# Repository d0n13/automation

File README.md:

# automation
Homebridge accessories

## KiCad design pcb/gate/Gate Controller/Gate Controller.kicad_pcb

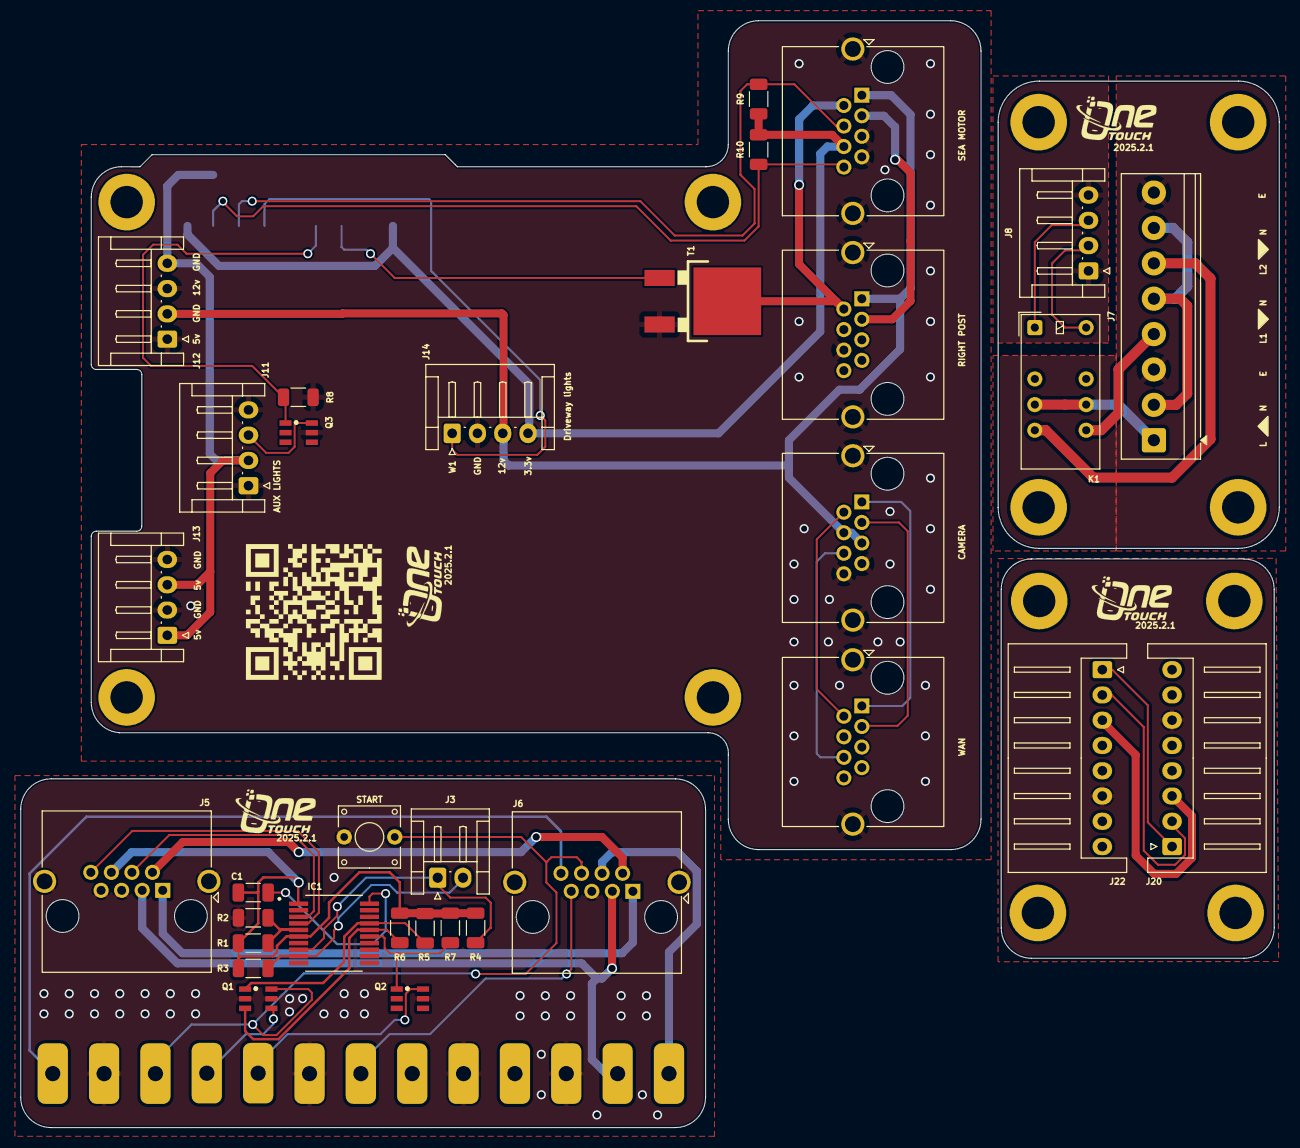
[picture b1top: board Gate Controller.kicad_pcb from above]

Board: 2 copper layers, 124.5 x 109.5 mm, 52 parts (1 on the bottom side), 39 nets.

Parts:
C1: 0.1uF; C_1206_3216Metric
G1, G2, G3, G4: LOGO; onetouchlogo
IC1: MCP23009-E_SS; SOP65P780X200-20N
J3: CN7; JST_EH_S2B-EH_1x02_P2.50mm_Horizontal
J4: CN1; Gate_Connector_2022
J5, J6, J16, J17: RJ45_Shielded; RJ45_Amphenol_RJHSE5380
J7: AUX; TerminalBlock_Phoenix_PT-1,5-8-3.5-H_1x08_P3.50mm_Horizontal
J8, J11: AUX; JST_EH_S4B-EH_1x04_P2.50mm_Horizontal
J12: Power; JST_EH_S4B-EH_1x04_P2.50mm_Horizontal
J13: Fiber Power; JST_EH_S4B-EH_1x04_P2.50mm_Horizontal
J14: Driveway lights; JST_EH_S4B-EH_1x04_P2.50mm_Horizontal
J15: POE Camera; RJ45_Amphenol_RJHSE5380
J18: Ethernet; RJ45_Amphenol_RJHSE5380
J20: Pi; JST_XH_S8B-XH-A_1x08_P2.50mm_Horizontal
J22: Post; JST_XH_S8B-XH-A_1x08_P2.50mm_Horizontal
K1: EC2-5SNU; Relay_DPDT_Kemet_EC2
MK1, MK2, MK3, MK4, MK5, MK6, MK7, MK8, MK9, MK10, MK11, MK12: M3.2; MountingHole_3.2mm_M3_DIN965_Pad
P1: pi; PinSocket_2x10_P2.54mm_Vertical_SMD
Q1, Q2, Q3: FDC6561AN; SSOT-6
R1: 1K; R_1206_3216Metric
R2: 15K; R_1206_3216Metric
R3, R4, R5, R6, R7, R8: 10k; R_1206_3216Metric
R9, R10: 1.8K; R_1206_3216Metric
SW1: START; TS-D015
T1: STD40NF10; D_PAK
U2: QRCode Github Automation

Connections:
3V3: C1.2, IC1.1 (VDD), IC1.6 (~RESET), J5.6, J14.4, J17.6, P1.1, P1.17, R1.1, R3.2, R4.2, R5.2, R6.2, R7.2, R9.2, R10.2
+5v: J11.2, J12.4, J13.1, J13.3, P1.2, P1.4
+12V: J12.2, J14.3, J15.4, J15.5, J16.1, J17.1
+12v: J5.1, J6.1
ANTENNA+: J4.1, J6.8
CN1_24v(FL): J4.12, J5.3, J6.3, J16.3, J17.3, J20.3, J22.3
CN1_(FL)-: J4.13, J6.4
E: J7.3, J7.8
GATE_LED_12V: J20.1, J22.1
GATE_LED_COM: J5.2, J6.2, J16.2, J17.2, T1.2 (D)
GND: J4.2, J4.6, J4.9, J4.11, J5.5, J5.7, J5.SH, J6.5, J6.SH, J8.1, J8.4, J11.1, J11.4, J12.1, J12.3, J13.2, J13.4, J14.2, J15.7, J15.8, J15.SH, J16.6, J16.SH, J17.5, J17.7, J17.SH, J18.SH, J20.6, J22.6, P1.6, P1.9, P1.14, P1.20, Q1.2, Q1.5, Q2.5, Q3.5, R2.2, R8.2, SW1.2, T1.3 (S)
L: J7.1, K1.4, K1.9
L1: J7.4, K1.8
L2: J7.6, K1.5
N: J7.2, J7.5, J7.7
unnamed: IC1.5 (ADDR), R1.2, R2.1
unnamed: IC1.8 (GP0), J3.1, R4.1
unnamed: IC1.9 (GP1), J3.2, R3.1
unnamed: IC1.15 (GP5), Q2.1, R7.1
unnamed: IC1.16 (GP6), Q1.3, R6.1
unnamed: IC1.17 (GP7), Q1.1, R5.1
unnamed: C1.1, IC1.20 (VSS)
unnamed: J8.2, K1.12
unnamed: J8.3, K1.1
unnamed: J11.3, Q3.6
unnamed: J15.1, J18.1
unnamed: J15.2, J18.2
unnamed: J15.3, J18.3
unnamed: J15.6, J18.6
unnamed: J20.2, J22.2
PEDST: J4.4, Q1.4
PH1: J4.7, J6.7
Rpi11: P1.11, Q3.1, R8.1
Rpi13: P1.13, T1.1 (G)
SCL1: IC1.3 (SCL), J5.4, J17.4, P1.5, R9.1
SDA1: IC1.4 (SDA), J5.8, J17.8, P1.3, R10.1
START: J4.3, J6.6, Q1.6, SW1.1
STOP: J4.5, Q2.6
W1: J14.1, P1.7

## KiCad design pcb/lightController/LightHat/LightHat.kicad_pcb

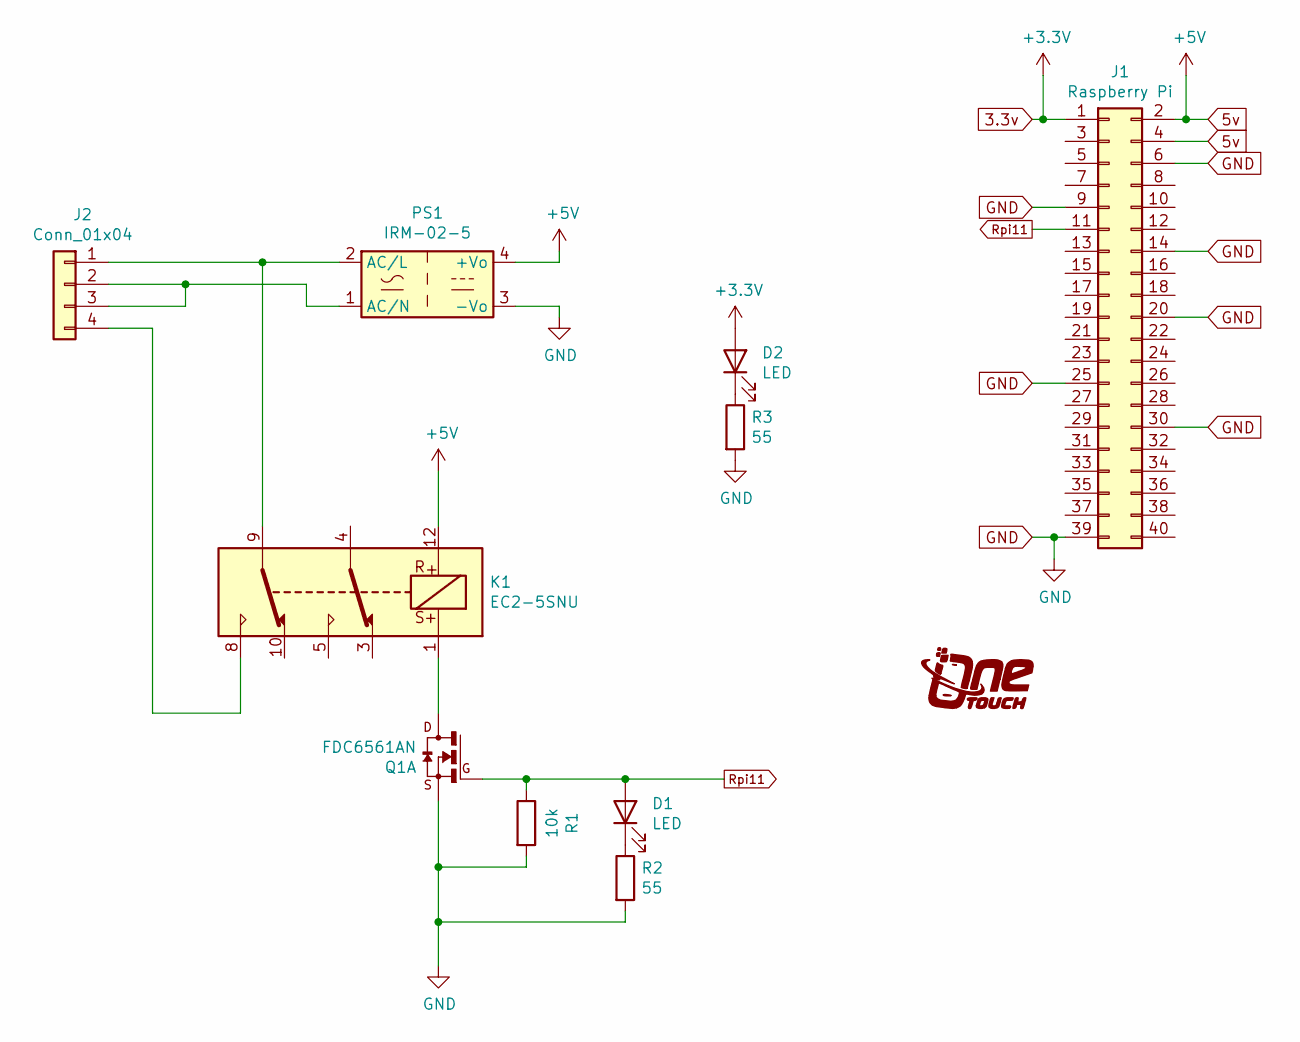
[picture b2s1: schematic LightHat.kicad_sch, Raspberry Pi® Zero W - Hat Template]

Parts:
D1, D2: LED; LED_0603_1608Metric
G1: LOGO; onetouchlogo
J1: Raspberry Pi; PinHeader_2x20_P2.54mm_Vertical
J2: Conn_01x04; TerminalBlock_bornier-4_P5.08mm
K1: EC2-5SNU; Relay_DPDT_Kemet_EC2
PS1: IRM-02-5; Converter_ACDC_MeanWell_IRM-02-xx_THT
Q1: FDC6561AN; SSOT-6
R1: 10k; R_0603_1608Metric_Pad0.98x0.95mm_HandSolder
R2, R3: 55; R_0805_2012Metric

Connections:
3.3v: D2.2 (A), J1.1
5v: J1.2, J1.4, K1.12, PS1.4 (+Vo)
GND: J1.6, J1.9, J1.14, J1.20, J1.25, J1.30, J1.39, PS1.3 (-Vo), Q1.5, R1.2, R2.2, R3.2
unnamed: D1.1 (K), R2.1
unnamed: D2.1 (K), R3.1
unnamed: J2.1, K1.9, PS1.2 (AC/L)
unnamed: J2.2, J2.3, PS1.1 (AC/N)
unnamed: J2.4, K1.8
unnamed: K1.1, Q1.6
Rpi11: D1.2 (A), J1.11, Q1.1, R1.1

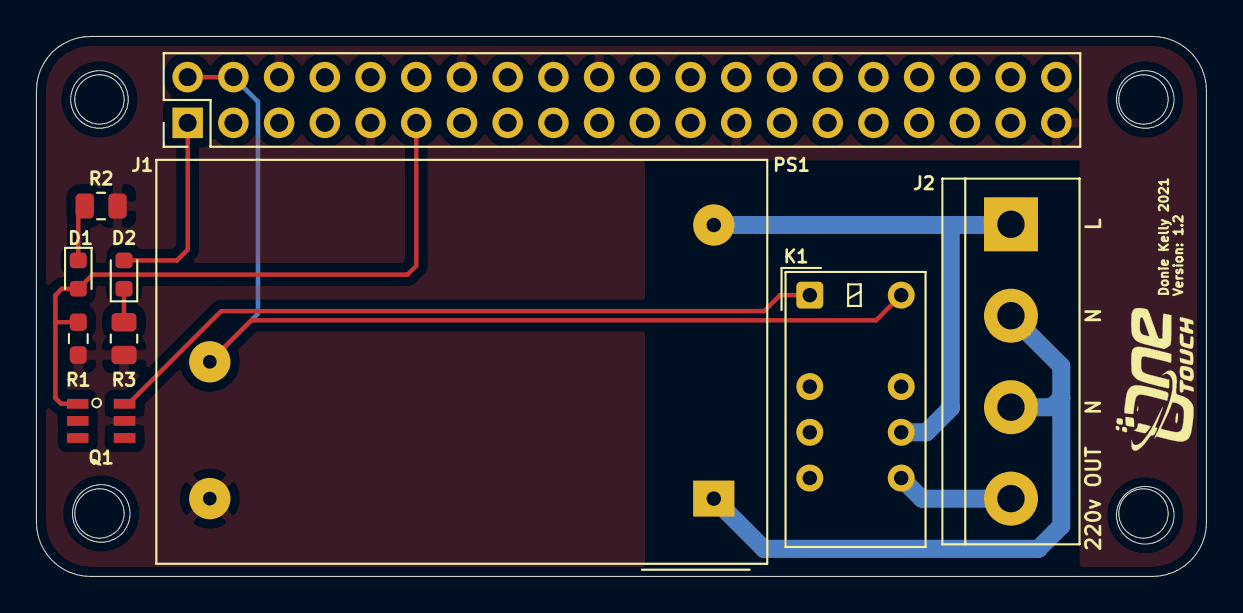
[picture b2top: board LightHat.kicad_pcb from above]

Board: 2 copper layers, 65.0 x 30.0 mm, 11 parts (0 on the bottom side), 10 nets.

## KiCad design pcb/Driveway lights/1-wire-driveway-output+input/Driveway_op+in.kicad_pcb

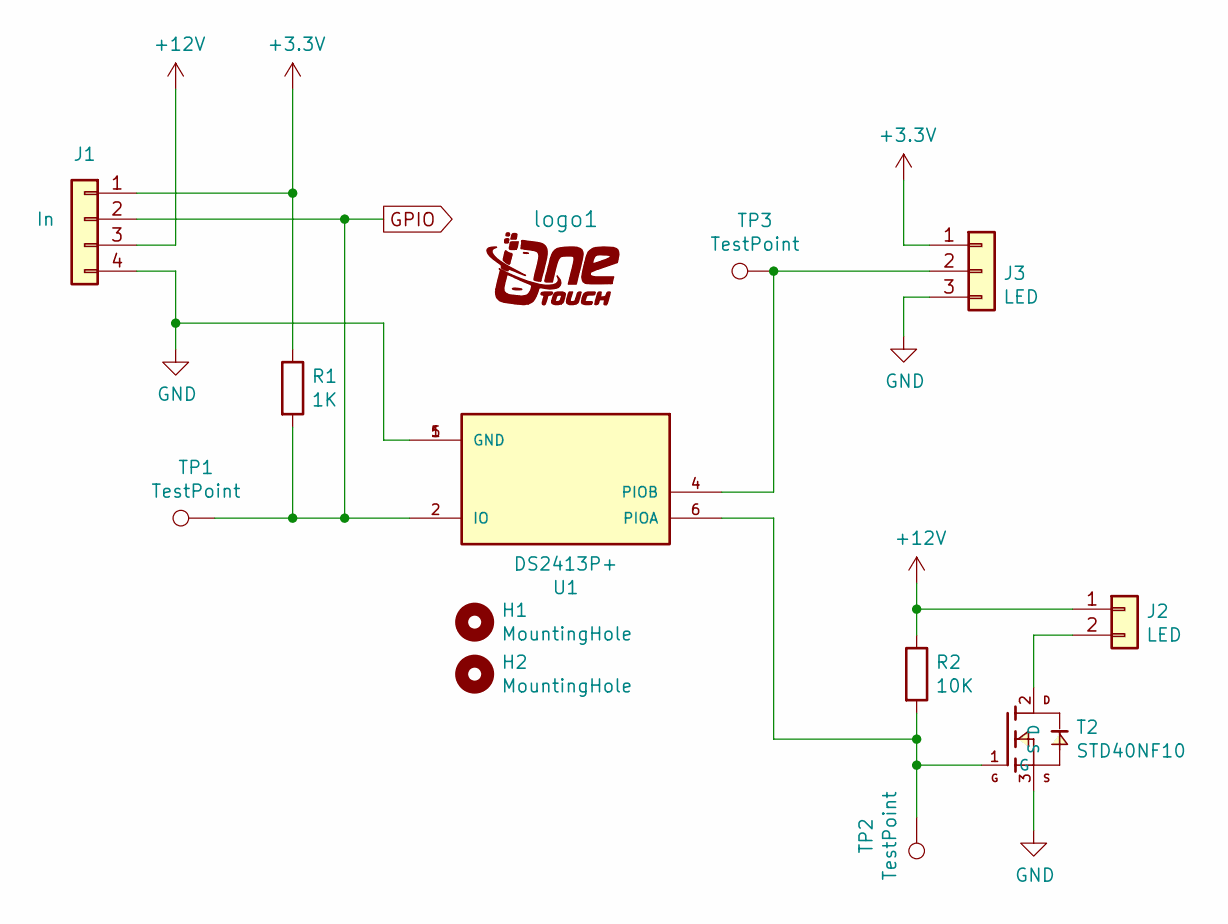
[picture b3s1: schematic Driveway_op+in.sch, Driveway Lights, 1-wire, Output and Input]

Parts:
H1, H2: MountingHole; MountingHole_2.1mm
J1: In; JST_EH_S4B-EH_1x04_P2.50mm_Horizontal
J2: LED; JST_EH_S2B-EH_1x02_P2.50mm_Horizontal
J3: LED; JST_XH_S3B-XH-A-1_1x03_P2.50mm_Horizontal
R1: 1K; R_1206_3216Metric
R2: 10K; R_1206_3216Metric
T2: STD40NF10; D_PAK
TP1, TP2, TP3: TestPoint; TestPoint_Pad_1.0x1.0mm
U1: DS2413P+; SOIC127P429X150-N
logo1: LOGO; onetouchlogo

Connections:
+3V3: J1.1, J3.1, R1.1
+12V: J1.3, J2.1, R2.1
GND: J1.4, J3.3, T2.3 (S), U1.1 (GND), U1.5 (GND)
GPIO: J1.2, R1.2, TP1.1, U1.2 (IO)
unnamed: J2.2, T2.2 (D)
unnamed: J3.2, TP3.1, U1.4 (PIOB)
unnamed: R2.2, T2.1 (G), TP2.1, U1.6 (PIOA)

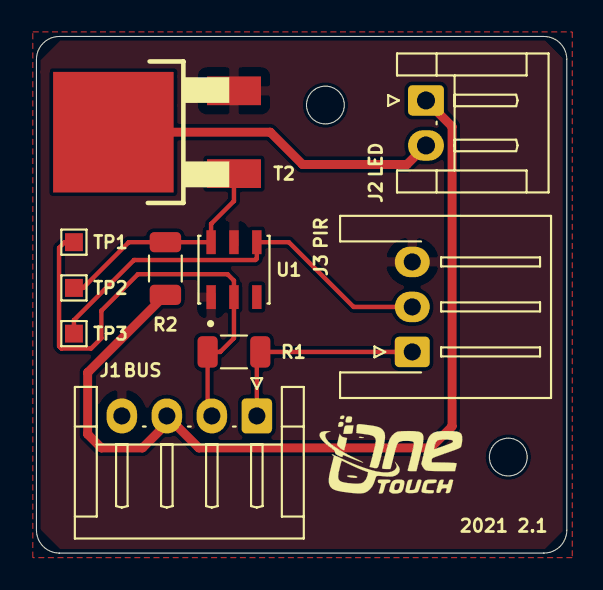
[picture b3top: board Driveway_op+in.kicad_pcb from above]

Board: 2 copper layers, 29.5 x 28.7 mm, 13 parts (0 on the bottom side), 7 nets.

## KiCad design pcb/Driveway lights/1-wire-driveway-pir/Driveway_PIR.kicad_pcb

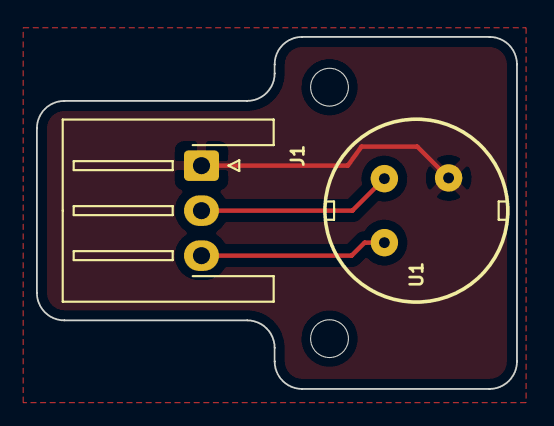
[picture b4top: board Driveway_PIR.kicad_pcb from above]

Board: 2 copper layers, 26.7 x 19.6 mm, 5 parts (1 on the bottom side), 3 nets.

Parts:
H1, H2: MountingHole; MountingHole_2.1mm
J1: LED; JST_XH_S3B-XH-A-1_1x03_P2.50mm_Horizontal
U1: EKMC1601111
logo1: LOGO; onetouchlogo

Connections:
GND1: J1.1, U1.1
unnamed: J1.2, U1.3
unnamed: J1.3, U1.2

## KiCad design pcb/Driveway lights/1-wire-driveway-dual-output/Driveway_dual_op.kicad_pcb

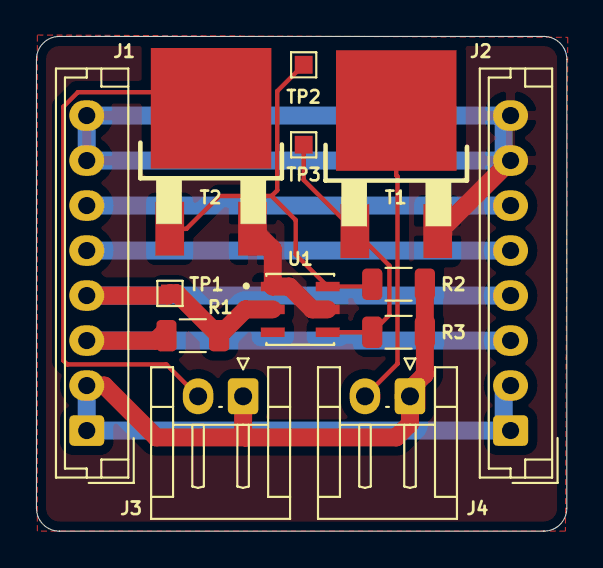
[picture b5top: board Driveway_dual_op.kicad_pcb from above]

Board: 2 copper layers, 29.5 x 27.5 mm, 14 parts (1 on the bottom side), 10 nets.

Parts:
J1: In; JST_EH_B8B-EH-A_1x08_P2.50mm_Vertical
J2: Out; JST_EH_B8B-EH-A_1x08_P2.50mm_Vertical
J3, J4: LED; JST_EH_S2B-EH_1x02_P2.50mm_Horizontal
R1: 1K; R_1206_3216Metric
R2, R3: 10K; R_1206_3216Metric
T1, T2: STD40NF10; D_PAK
TP1, TP2, TP3: TestPoint; TestPoint_Pad_1.0x1.0mm
U1: DS2413P+; SOIC127P429X150-N
logo1: LOGO; onetouchlogo

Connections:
+3V3: J1.3, J2.3, R1.1
+12V: J1.1, J1.2, J2.1, J2.2, J3.1, J4.1, R2.1, R3.1
GND: J1.7, J1.8, J2.7, J2.8, T1.P$3, T2.P$3, U1.1, U1.5
GPIO: J1.4, J2.4, R1.2, TP1.1, U1.2
unnamed: J1.5, J2.5
unnamed: J1.6, J2.6
unnamed: J3.2, T2.P$2
unnamed: J4.2, T1.P$2
unnamed: R2.2, T2.P$1, TP2.1, U1.6
unnamed: R3.2, T1.P$1, TP3.1, U1.4

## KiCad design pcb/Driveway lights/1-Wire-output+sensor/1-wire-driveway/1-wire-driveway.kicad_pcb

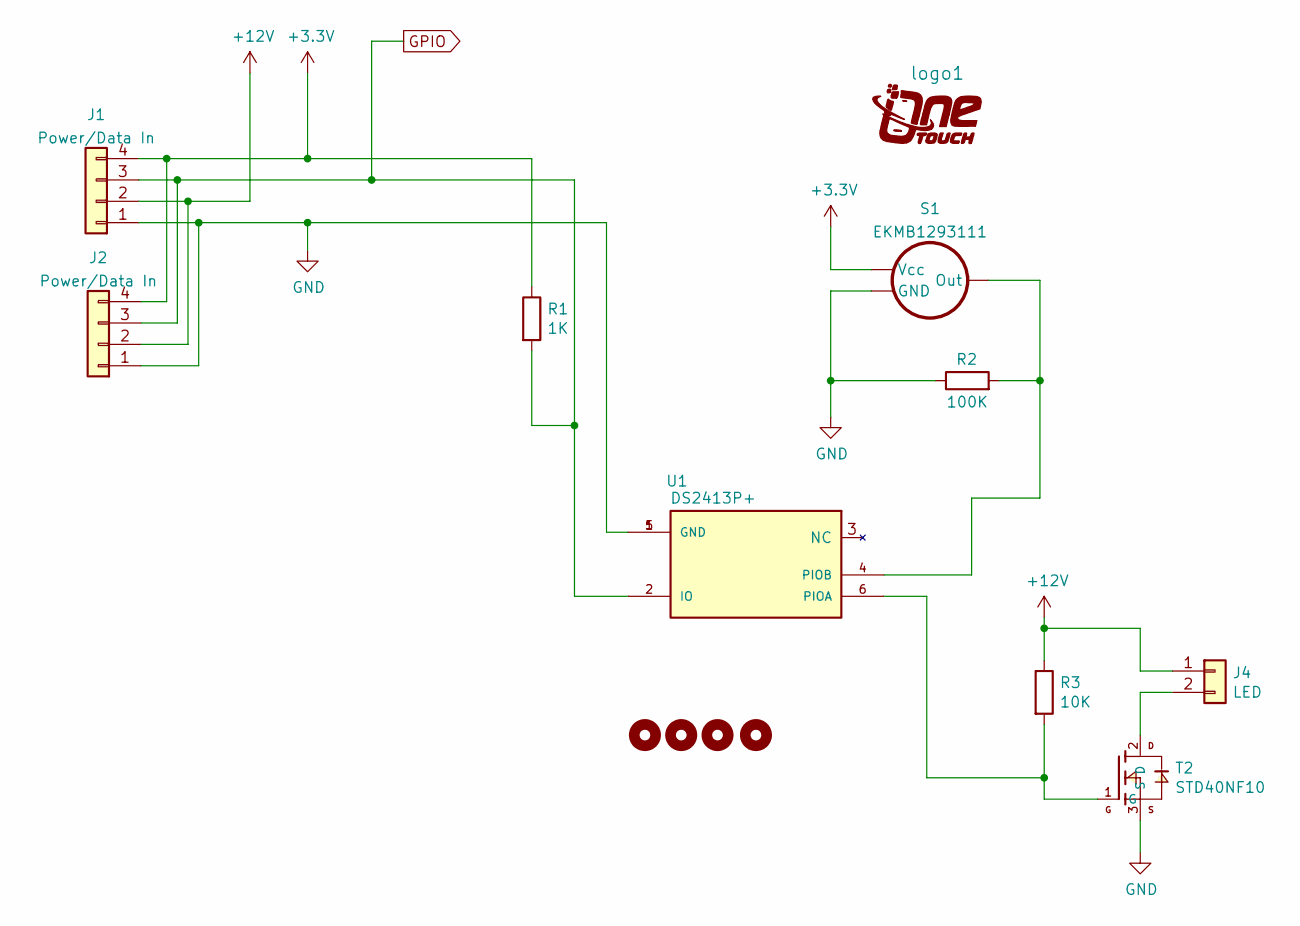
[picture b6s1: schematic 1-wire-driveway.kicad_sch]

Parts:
H1, H2, H3, H4: MountingHole; MountingHole_3.2mm_M3
J1, J2: Power/Data In; PhoenixContact_MCV_1,5_4-G-5.08_1x04_P5.08mm_Vertical
J4: LED; JST_XH_B2B-XH-AM_1x02_P2.50mm_Vertical
R1: 1K; R_1206_3216Metric
R2: 100K; R_1206_3216Metric
R3: 10K; R_1206_3216Metric
S1: EKMB1293111
T2: STD40NF10; D_PAK
U1: DS2413P+; SOIC127P429X150-N
logo1: LOGO; onetouchlogo

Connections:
+3V3: J1.4, J2.4, R1.1, S1.1 (Vcc)
+12V: J1.2, J2.2, J4.1, R3.1
GND: J1.1, J2.1, R2.1, S1.2 (GND), T2.3 (S), U1.1 (GND), U1.5 (GND)
GPIO: J1.3, J2.3, R1.2, U1.2 (IO)
unnamed: J4.2, T2.2 (D)
unnamed: R2.2, S1.3 (Out), U1.4 (PIOB)
unnamed: R3.2, T2.1 (G), U1.6 (PIOA)

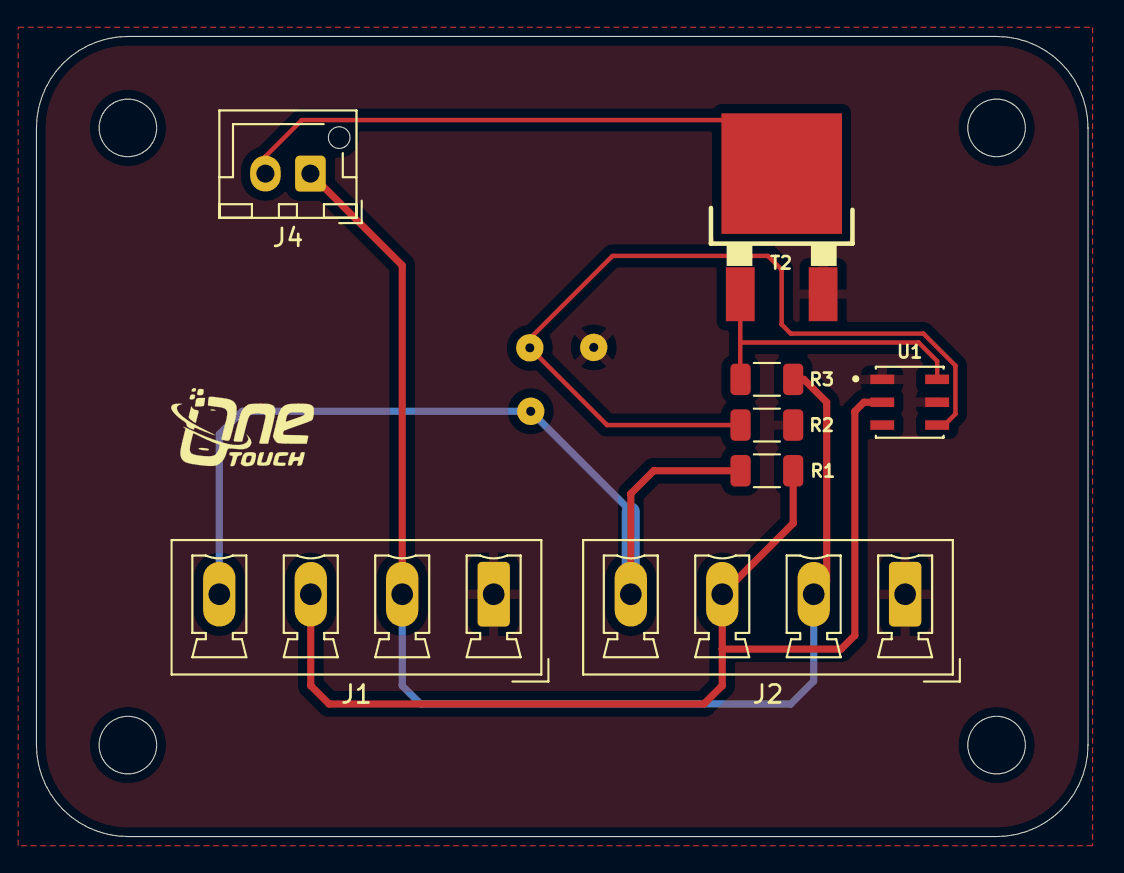
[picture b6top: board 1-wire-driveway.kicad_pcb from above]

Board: 2 copper layers, 58.4 x 44.5 mm, 14 parts (1 on the bottom side), 7 nets.

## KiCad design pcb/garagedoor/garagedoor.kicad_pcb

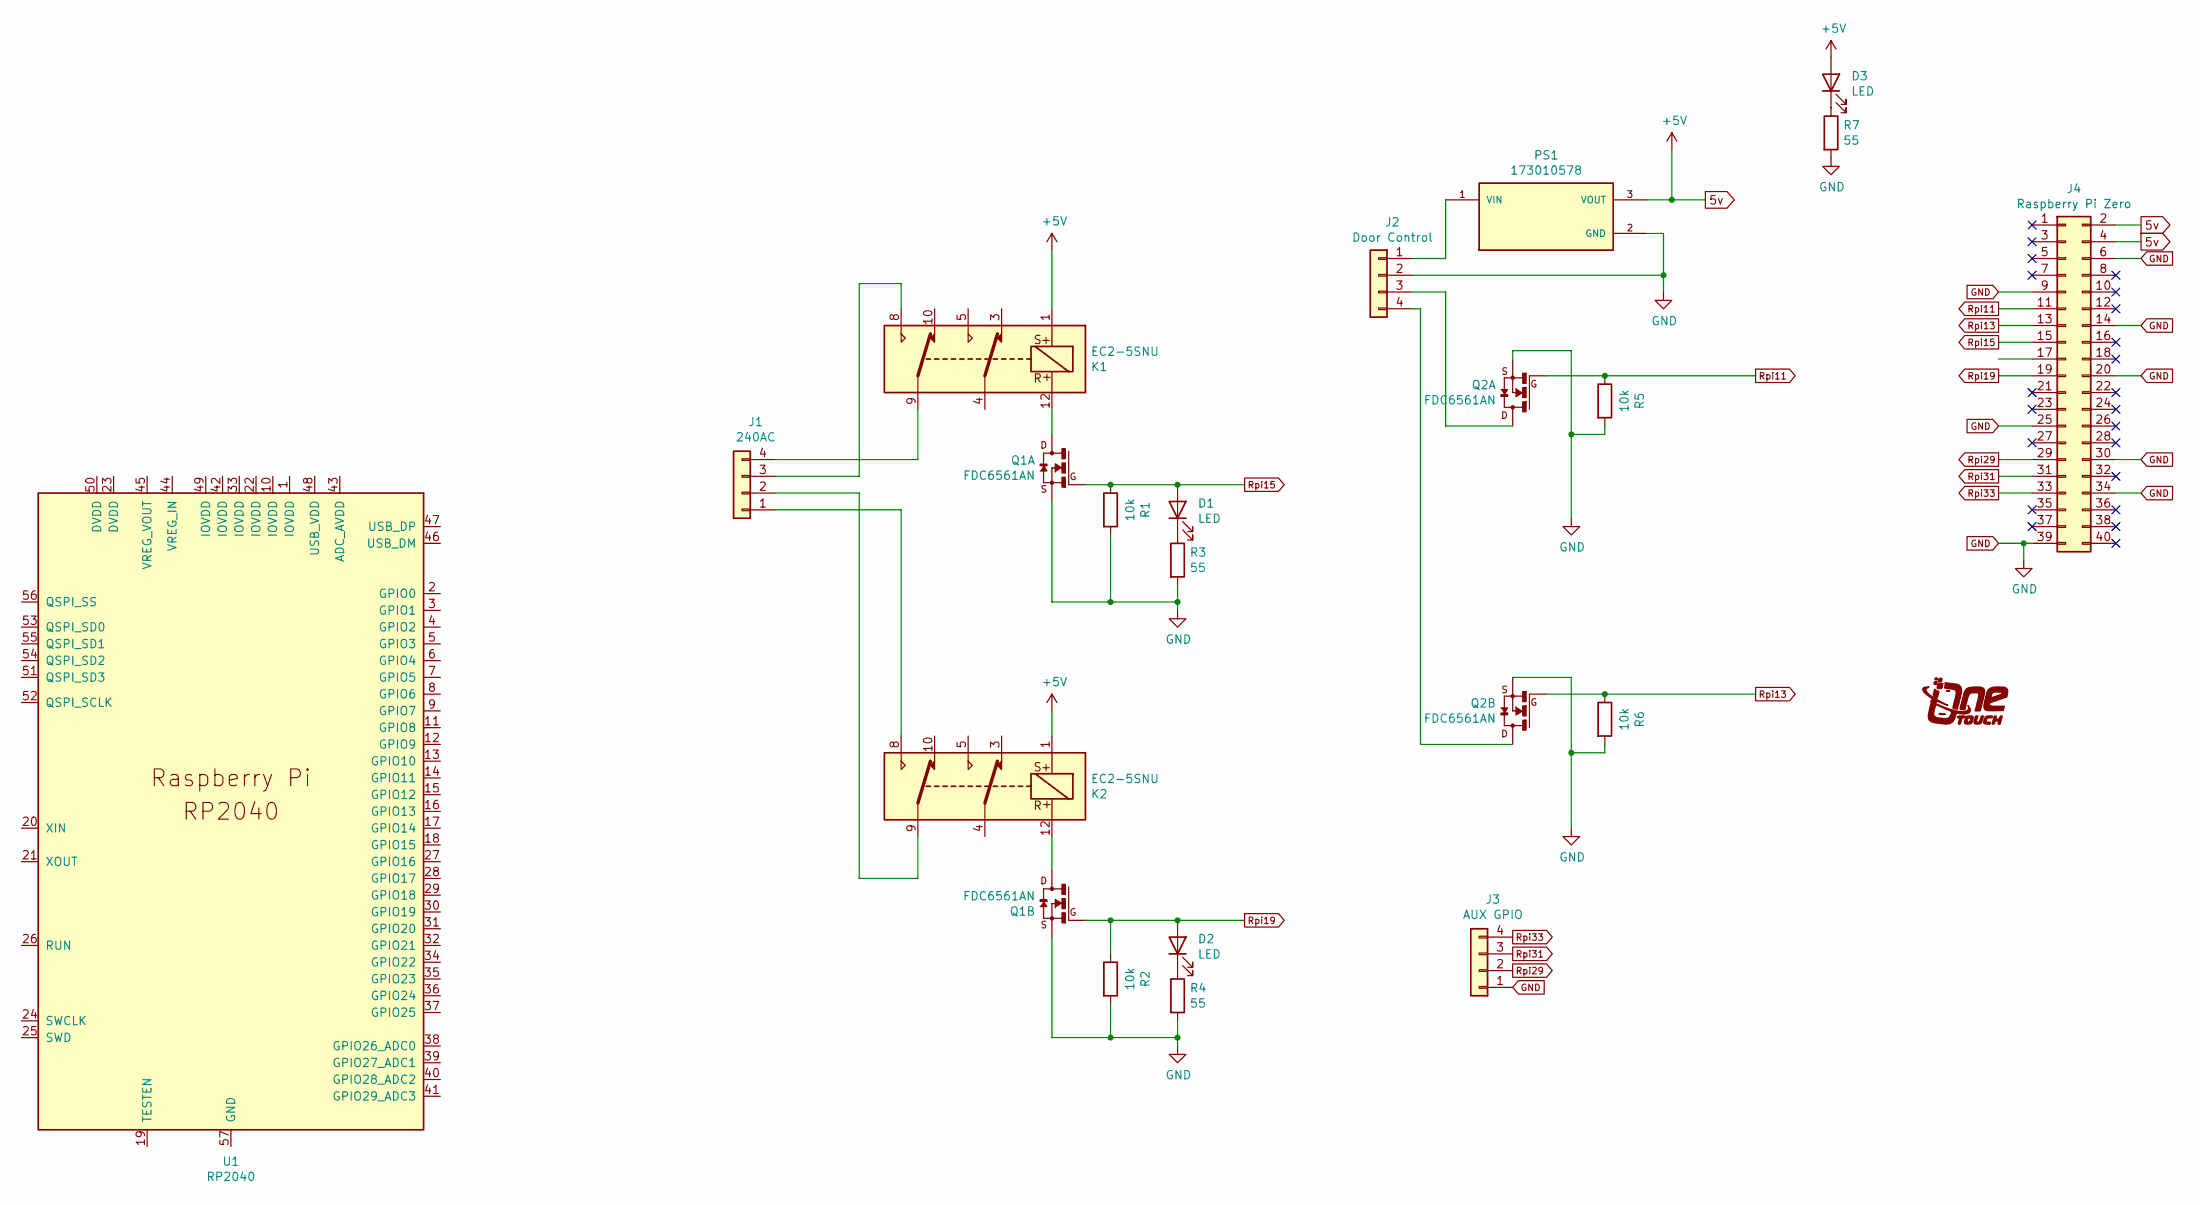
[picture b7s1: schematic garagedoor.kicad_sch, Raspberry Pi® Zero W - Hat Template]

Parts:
D1, D2, D3: LED; LED_0603_1608Metric
G1: LOGO; onetouchlogo
J1: 240AC; TerminalBlock_bornier-4_P5.08mm
J2: Door Control; JST_EH_S4B-EH_1x04_P2.50mm_Horizontal
J3: AUX GPIO; JST_EH_S4B-EH_1x04_P2.50mm_Horizontal
J4: Raspberry Pi Zero; PinHeader_2x20_P2.54mm_Vertical
K1, K2: EC2-5SNU; Relay_DPDT_Kemet_EC2
PS1: 173010578; CONV_173010578; PARTREV 1.0
Q1, Q2: FDC6561AN; SSOT-6
R1, R2, R5, R6: 10k; R_0603_1608Metric_Pad0.98x0.95mm_HandSolder
R3, R4, R7: 55; R_0805_2012Metric
U1: RP2040

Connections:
5v: D3.2 (A), J4.2, J4.4, K1.1, K2.1, PS1.3 (VOUT)
GND: J2.2, J3.1, J4.6, J4.9, J4.14, J4.20, J4.25, J4.30, J4.34, J4.39, PS1.2 (GND), Q1.2, Q1.5, Q2.2, Q2.5, R1.2, R2.2, R3.2, R4.2, R5.2, R6.2, R7.2
unnamed: D1.1 (K), R3.1
unnamed: D2.1 (K), R4.1
unnamed: D3.1 (K), R7.1
unnamed: J1.1, K2.8
unnamed: J1.2, K2.9
unnamed: J1.3, K1.8
unnamed: J1.4, K1.9
unnamed: J2.1, PS1.1 (VIN)
unnamed: J2.3, Q2.6
unnamed: J2.4, Q2.4
unnamed: K1.12, Q1.6
unnamed: K2.12, Q1.4
Rpi11: J4.11, Q2.1, R5.1
Rpi13: J4.13, Q2.3, R6.1
Rpi15: D1.2 (A), J4.15, Q1.1, R1.1
Rpi19: D2.2 (A), J4.19, Q1.3, R2.1
Rpi29: J3.2, J4.29
Rpi31: J3.3, J4.31
Rpi33: J3.4, J4.33

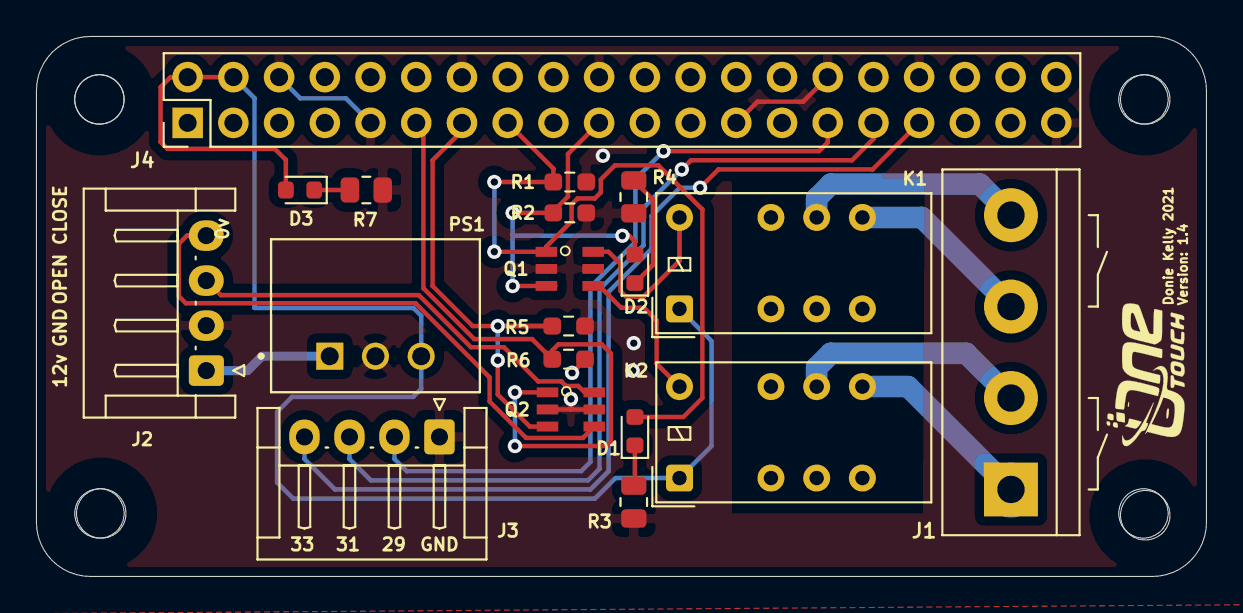
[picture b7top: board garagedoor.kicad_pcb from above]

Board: 2 copper layers, 65.0 x 30.0 mm, 20 parts (0 on the bottom side), 21 nets.

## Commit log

2023-03-25 Moved to github
2023-03-25 Updated spaces to tabs
2023-03-25 deleted
2023-03-25 spaces to tabs
2024-12-16 latest updates
2024-12-16 Add template
2024-12-17 Updated gate controller pcb to 2024.1.0
2024-12-26 Updated opener to report state after opening or closing
2024-12-26 Updated pcb
2024-12-28 Latest modules
2024-12-30 Code changes
2025-01-05 Fixed openiong and closing logic
2025-01-06 Removed AP stuff
2025-01-06 Fixes for state
2025-02-05 Update instructions about homebridge home folder
2025-02-05 Fixed open and close state updates
2025-07-27 reworked to add i2c pullups and reduces unusedd components
2025-07-27 Update with latest changes to fix comms issues
2025-07-31 Updated solder pads for ic1
2025-09-10 Fixed gpio numbering for new pcb Flash light on gate open/close Read gate light state
2025-09-10 Fixde state feedback Read state of lights from gpio

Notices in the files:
pcb/garagedoor/garagedoor.kicad_pcb:
License: MIT - Copyright 2018 StudioPieters®
